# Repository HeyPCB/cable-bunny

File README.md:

# Cable Bunny

**Is it a charge-only cable? Ask the bunny.**

Cable Bunny is a passive USB-C cable tester shaped like a bunny. Plug both ends of a cable into the two USB-C receptacles that are its feet and press its nose: a CR2032 drives every line of the first receptacle, and every line that reaches the second one lights its own LED in the bunny's ears, VBUS, GND and CC in the left ear and D+, D- and SBU in the right. A heart LED says the cell is good. There is no MCU and no firmware.

| Layers | Size | Parts | Nets | Connections routed | Vias | ERC errors | DRC errors / unconnected / parity | BOM @100 |
|---|---|---|---|---|---|---|---|---|
| 2 | 40.1 x 96.2 mm | 25 | 22 | 58 -> 0 open | 27 | 0 | 0 / 0 / 0 | $0.95 |

**Not fabricated, assembled or powered yet.** Every number on this page is measured by KiCad 10.0.6 on
the files in this repository ([`report.json`](report.json), [`measured.json`](measured.json)) or read
from the live JLC/LCSC catalogue ([`bom_cost.json`](bom_cost.json)).

| | |
|---|---|
| Spec, power budget, BOM | [`SPEC.md`](SPEC.md) |
| Store copy | [`STORE_COPY.md`](STORE_COPY.md) |
| KiCad 10 project | [`kicad/`](kicad/) |
| Gerbers, drill, BOM, CPL, STEP, schematic PDF | [`fab/`](fab/) |
| Firmware | none: no MCU on this board |
| Renders | [front](media/top.png), [back](media/bottom.png), [hero](media/hero.png), [Circuit World thumbnail](media/circuit-world.png) |
| Brief and generator | [`design/`](design/) |

## What's on it

- **Source foot (J1):** every line (VBUS, CC, D+, D-, SBU) driven from the test rail through its own 150 Ω, both rows of the receptacle joined so either plug orientation works.
- **Far foot (J2):** each arriving line lights its own 0603 LED through 220 Ω to the far receptacle's ground, which reaches the cell only through the cable's ground wire; the GND LED (330 Ω from the rail) proves that wire. The far shell is not connected.
- **Nose:** a TS-1187A button that connects the cell only while pressed, through a B5819W Schottky that stops a powered cable from back-feeding the lithium cell.
- **Heart:** a red LED on the test rail: if the heart lights and an ear LED doesn't, that wire is broken.
- **Power:** one CR2032 in a Keystone 3034 holder, about 12,000 three-second tests (SPEC.md).

## Finish

White solder mask, Black silkscreen, ENIG copper finish, 1.6 mm FR4, top-side SMT assembly (J1, J2: an SMD part whose shell legs go through plated holes, soldered on the same SMT line).
The gold art is bare copper under a mask opening (ENIG), drawn with its own keep-out so no track runs
under it. The QR code on the back opens [https://heypcb.ai/world/b/e8dc1e4d9cfb](https://heypcb.ai/world/b/e8dc1e4d9cfb).

## How it was made

Designed with the HeyPCB method on KiCad 10.0.6, headless, by the `heypcb-kicad` pipeline: a written
brief composed from reusable circuit blocks, every pin from KiCad's own symbol library, every part bound
to an LCSC number from a dated catalogue read, then ERC, a netlist round trip, locked placement,
Freerouting 2.4.1, pours, silkscreen and board art, DRC with schematic parity, DFM and a fab gate,
each stage gated by a measurement. `design/make_brief.py` regenerates the brief (outline, part
locks and art) from code.

Part of the [heypcb.ai merch collection](https://github.com/HeyPCB/merch).

## License

Hardware: [CERN-OHL-S v2](LICENSE). KiCad's symbol, footprint and 3D
libraries used in the design are CC-BY-SA 4.0 with the KiCad library exception.

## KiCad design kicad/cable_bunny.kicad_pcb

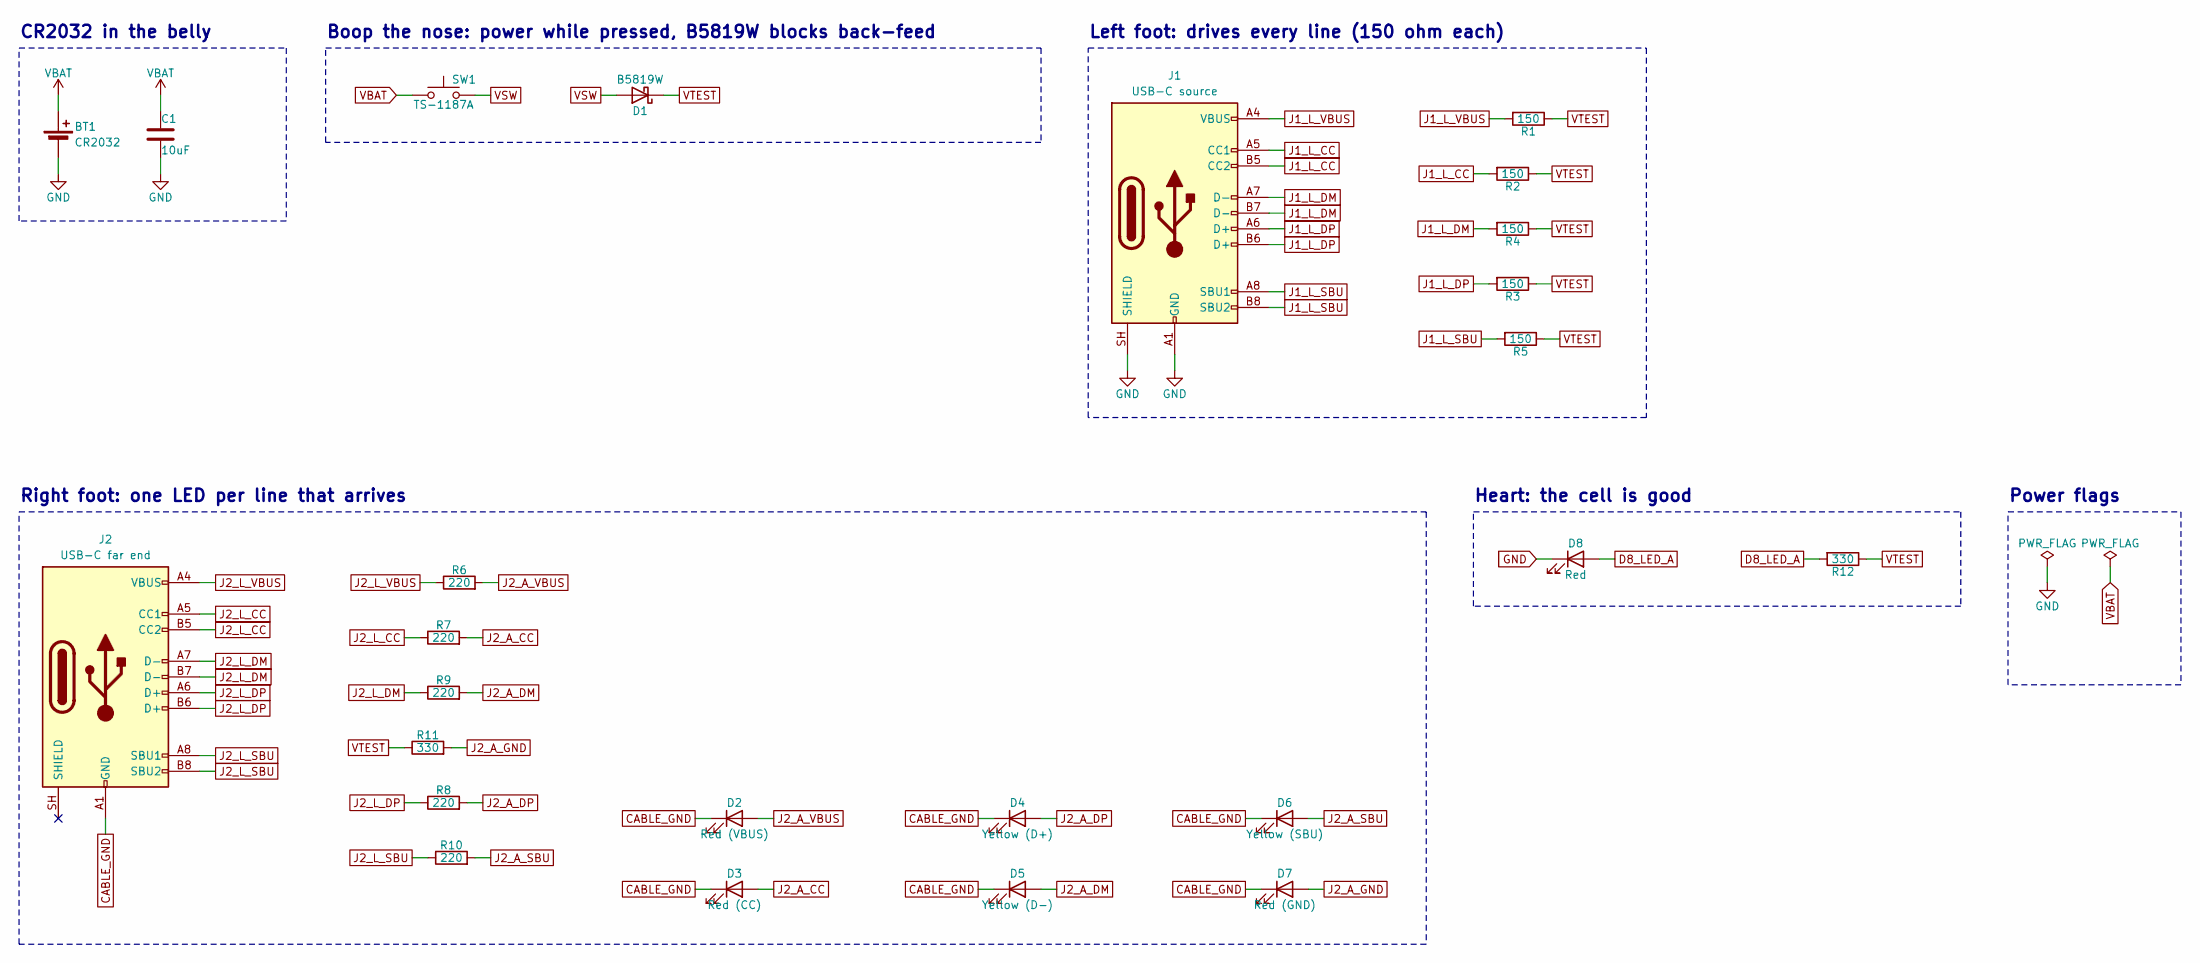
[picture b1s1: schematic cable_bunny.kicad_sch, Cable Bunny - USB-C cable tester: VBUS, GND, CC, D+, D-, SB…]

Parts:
BT1: CR2032; BatteryHolder_Keystone_3034_1x20mm; MPN 3034TR; LCSC C5213768
C1: 10uF; C_0805_2012Metric; MPN CL21A106KAYNNNE; LCSC C15850
D1: B5819W; D_SOD-123; MPN B5819W SL; LCSC C8598
D2: Red (VBUS); LED_0603_1608Metric; MPN KT-0603R; LCSC C2286
D3: Red (CC); LED_0603_1608Metric; MPN KT-0603R; LCSC C2286
D4: Yellow (D+); LED_0603_1608Metric; MPN KT-0603Y; LCSC C2287
D5: Yellow (D-); LED_0603_1608Metric; MPN KT-0603Y; LCSC C2287
D6: Yellow (SBU); LED_0603_1608Metric; MPN KT-0603Y; LCSC C2287
D7: Red (GND); LED_0603_1608Metric; MPN KT-0603R; LCSC C2286
D8: Red; LED_0603_1608Metric; MPN KT-0603R; LCSC C2286
J1: USB-C source; USB_C_Receptacle_HRO_TYPE-C-31-M-12; MPN TYPE-C-31-M-12; LCSC C165948
J2: USB-C far end; USB_C_Receptacle_HRO_TYPE-C-31-M-12; MPN TYPE-C-31-M-12; LCSC C165948
R1, R2, R3, R4, R5: 150; R_0603_1608Metric; MPN 0603WAF1500T5E; LCSC C22808
R6, R7, R8, R9, R10: 220; R_0603_1608Metric; MPN 0603WAF2200T5E; LCSC C22962
R11, R12: 330; R_0603_1608Metric; MPN 0603WAF3300T5E; LCSC C23138
SW1: TS-1187A; SW_Push_1P1T_XKB_TS-1187A; MPN TS-1187A-B-A-B; LCSC C318884

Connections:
CABLE_GND: D2.1 (K), D3.1 (K), D4.1 (K), D5.1 (K), D6.1 (K), D7.1 (K), J2.A1 (GND), J2.A12 (GND), J2.B1 (GND), J2.B12 (GND)
D8_LED_A: D8.2 (A), R12.2
GND: BT1.2 (-), C1.2, D8.1 (K), J1.A1 (GND), J1.A12 (GND), J1.B1 (GND), J1.B12 (GND), J1.SH (SHIELD)
J1_L_CC: J1.A5 (CC1), J1.B5 (CC2), R2.2
J1_L_DM: J1.A7 (D-), J1.B7 (D-), R4.2
J1_L_DP: J1.A6 (D+), J1.B6 (D+), R3.2
J1_L_SBU: J1.A8 (SBU1), J1.B8 (SBU2), R5.2
J1_L_VBUS: J1.A4 (VBUS), J1.A9 (VBUS), J1.B4 (VBUS), J1.B9 (VBUS), R1.2
J2_A_CC: D3.2 (A), R7.2
J2_A_DM: D5.2 (A), R9.2
J2_A_DP: D4.2 (A), R8.2
J2_A_GND: D7.2 (A), R11.2
J2_A_SBU: D6.2 (A), R10.2
J2_A_VBUS: D2.2 (A), R6.2
J2_L_CC: J2.A5 (CC1), J2.B5 (CC2), R7.1
J2_L_DM: J2.A7 (D-), J2.B7 (D-), R9.1
J2_L_DP: J2.A6 (D+), J2.B6 (D+), R8.1
J2_L_SBU: J2.A8 (SBU1), J2.B8 (SBU2), R10.1
J2_L_VBUS: J2.A4 (VBUS), J2.A9 (VBUS), J2.B4 (VBUS), J2.B9 (VBUS), R6.1
VBAT: BT1.1 (+), C1.1, SW1.1
VSW: D1.2 (A), SW1.2
VTEST: D1.1 (K), R1.1, R2.1, R3.1, R4.1, R5.1, R11.1, R12.1

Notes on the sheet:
CR2032 in the belly
Boop the nose: power while pressed, B5819W blocks back-feed
Left foot: drives every line (150 ohm each)
Right foot: one LED per line that arrives
Heart: the cell is good
Power flags

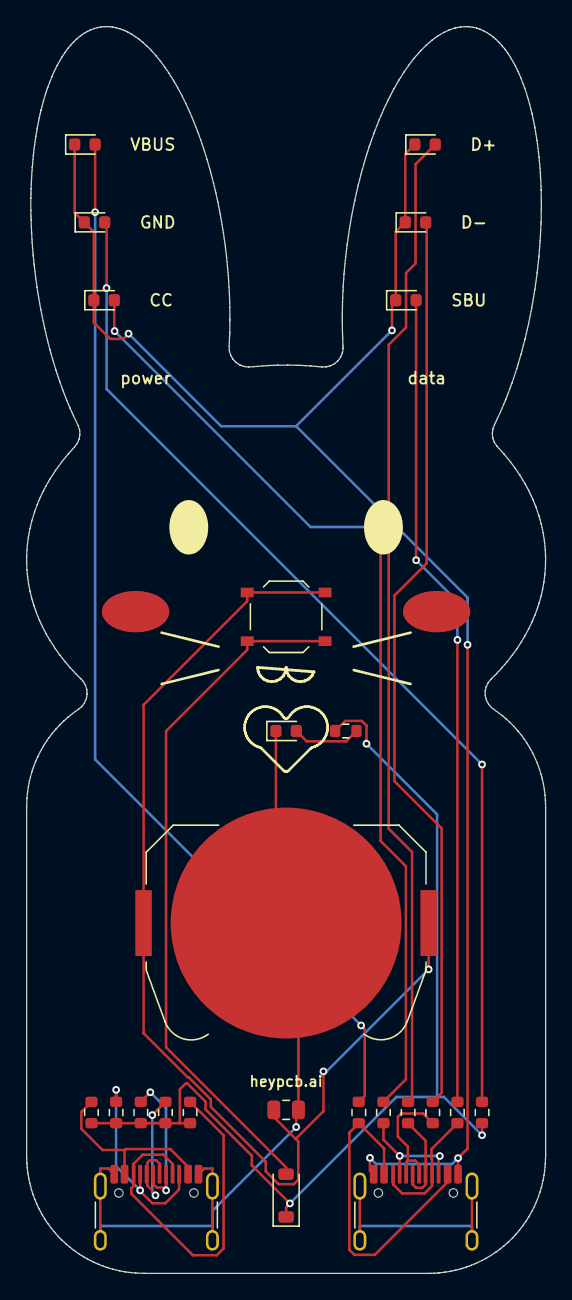
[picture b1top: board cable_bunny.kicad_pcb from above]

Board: 2 copper layers, 40.0 x 96.1 mm, 25 parts (0 on the bottom side), 22 nets.

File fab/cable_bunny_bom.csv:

"Reference","Value","Footprint","MPN","LCSC","Qty"
"BT1","CR2032","Battery:BatteryHolder_Keystone_3034_1x20mm","3034TR","C5213768","1"
"C1","10uF","Capacitor_SMD:C_0805_2012Metric","CL21A106KAYNNNE","C15850","1"
"D1","B5819W","Diode_SMD:D_SOD-123","B5819W SL","C8598","1"
"D2","Red (VBUS)","LED_SMD:LED_0603_1608Metric","KT-0603R","C2286","1"
"D3","Red (CC)","LED_SMD:LED_0603_1608Metric","KT-0603R","C2286","1"
"D4","Yellow (D+)","LED_SMD:LED_0603_1608Metric","KT-0603Y","C2287","1"
"D5","Yellow (D-)","LED_SMD:LED_0603_1608Metric","KT-0603Y","C2287","1"
"D6","Yellow (SBU)","LED_SMD:LED_0603_1608Metric","KT-0603Y","C2287","1"
"D7","Red (GND)","LED_SMD:LED_0603_1608Metric","KT-0603R","C2286","1"
"D8","Red","LED_SMD:LED_0603_1608Metric","KT-0603R","C2286","1"
"J1","USB-C source","Connector_USB:USB_C_Receptacle_HRO_TYPE-C-31-M-12","TYPE-C-31-M-12","C165948","1"
"J2","USB-C far end","Connector_USB:USB_C_Receptacle_HRO_TYPE-C-31-M-12","TYPE-C-31-M-12","C165948","1"
"R1,R2,R3,R4,R5","150","Resistor_SMD:R_0603_1608Metric","0603WAF1500T5E","C22808","5"
"R6,R7,R8,R9,R10","220","Resistor_SMD:R_0603_1608Metric","0603WAF2200T5E","C22962","5"
"R11,R12","330","Resistor_SMD:R_0603_1608Metric","0603WAF3300T5E","C23138","2"
"SW1","TS-1187A","Button_Switch_SMD:SW_Push_1P1T_XKB_TS-1187A","TS-1187A-B-A-B","C318884","1"
